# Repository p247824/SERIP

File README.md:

# SERIP — Sistema Embarcado Reativo de Iluminação e Presença

Sistema embarcado desenvolvido na disciplina **EA801 — Laboratório de Projetos de Sistemas Embarcados**, da Faculdade de Engenharia Elétrica e de Computação (FEEC/UNICAMP).

O SERIP combina visualização espectral de áudio em tempo real e controle de iluminação baseado na presença humana, utilizando a plataforma [BitDogLab V7](https://github.com/BitDogLab/BitDogLab), com RP2350. O Projeto 3 consolida a integração do hardware em uma PCB dedicada, mantendo o firmware do Projeto 2.

## Visão geral

### Funcionalidades

- Análise de áudio por FFT de 256 pontos, à frequência de amostragem de 16 kHz.
- Aquisição por ADC e DMA com buffers alternados, processamento em dois núcleos.
- Visualização em matriz de LEDs monocromática 32 × 8, com quatro MAX7219 em cascata.
- Controle automático por sensor radar de presença HLK-LD2410B.
- Modos automático, reativo e desligado, selecionáveis pelo usuário.
- Display OLED com telemetria, gráfico espectral e menu de calibração.
- Placa adaptadora dedicada, eliminando a protoboard utilizada na etapa anterior.

## Evolução do projeto

| Etapa | Desenvolvimento |
| --- | --- |
| Projeto 1 | Protótipo inicial com captação de áudio, matriz de LEDs e interface OLED na BitDogLab. |
| Projeto 2 | Matriz externa MAX7219, radar HLK-LD2410B e expansão da interface e da análise espectral. |
| Projeto 3 | Integração em placa de circuito impresso dedicada, projetada no KiCad para fabricação no SATE/FEEC. |

## Arquitetura

O núcleo 1 do RP2350 é responsável por aquisição do áudio, remoção de offset DC, aplicação da janela Hann e cálculo da FFT. O núcleo 0 gerencia o radar, a comunicação SPI com a matriz, os botões e o OLED. A comunicação entre os núcleos é feita pela FIFO multicore.

| Parâmetro | Valor |
| --- | --- |
| Frequência de amostragem | 16 kHz |
| FFT | 256 pontos |
| Duração de cada bloco | 16 ms |
| Limite de Nyquist | 8 kHz |
| Espaçamento espectral | 62,5 Hz |
| Resolução nominal da matriz | 250 Hz por coluna |
| Comunicação com a matriz | SPI0, 4 MHz |
| Comunicação OLED | I²C1, 400 kHz |

## Hardware

| Componente | Sinal / GPIO |
| --- | --- |
| Microfone MAX4466 (onboard) | GPIO28 — ADC2 |
| Sensor HLK-LD2410B | GPIO4 — OUT |
| Matriz MAX7219 | GPIO17 — CS; GPIO18 — SCK; GPIO19 — DIN |
| OLED SSD1306 | GPIO2 — SDA; GPIO3 — SCL |
| Botão A | GPIO5 |
| Botão B | GPIO6 |
| Botão C | GPIO10 |
| Joystick | GPIO27 — X; GPIO26 — Y |

O sensor e a matriz utilizam alimentação de 5 V e terra comum. A saída digital do radar é de 3,3 V; os pinos UART permanecem sem conexão nesta versão. Confira a correspondência física do IDC de 14 pinos, a polaridade e a orientação dos módulos antes de ligar.

### PCB do Projeto 3

- Dimensões: 52 × 46 mm.
- Face única de cobre (B.Cu), sem vias.
- Largura de trilhas de 0,90 mm, conforme a versão final descrita no relatório.
- J1: interface IDC-14 da BitDogLab.
- J2: conexão da matriz MAX7219.
- J3: conexão do radar HLK-LD2410B (passo de 1,27 mm).
- Plano de terra e contorno de recorte definidos no KiCad.

[Consultar esquemático da PCB](docs/images/esquematico_pcb.png) · [Consultar relatório técnico](docs/Relatorio_Projeto_3.pdf)

O esquemático de montagem do Projeto 2, fornecido com o código, também está disponível em [PDF](docs/esquematico_montagem.pdf) e [SVG](docs/esquematico_montagem.svg). Os arquivos editáveis do KiCad, a biblioteca de footprints e os Gerbers de fabricação do Projeto 3 estão disponíveis em [pcb-prototyping/](pcb-prototyping/). Consulte o [guia do hardware](pcb-prototyping/README.md) para abrir o projeto ou acessar os arquivos de fabricação.

## Implementação física

*Protótipo do Projeto 3 em funcionamento, com os periféricos conectados à BitDogLab V7 por meio da PCB dedicada.*

## Operação

| Comando | Ação |
| --- | --- |
| Botão A | Alterna entre automático (presença → iluminação ambiente, ausência → espera), reativo e desligado. |
| Botão B | Alterna entre painel de estado e gráfico espectral. |
| Botão C | Abre ou fecha o menu de configuração. |
| Joystick Y | Seleciona o parâmetro. |
| Joystick X | Ajusta o valor. |

| Parâmetro | Padrão | Faixa |
| --- | ---: | ---: |
| Limiar de ruído | 20 | 0–500 |
| Teto de energia | 800 | 100–3000 |
| Ganho visual | 1,50 | 0,5–5,0 |
| Velocidade de queda | 1,00 | 0,1–5,0 |

Os ajustes são mantidos em RAM e retornam aos valores padrão após a reinicialização.

## Compilação e gravação

### Pré-requisitos

- BitDogLab V7 com Raspberry Pi Pico 2 W (RP2350).
- Raspberry Pi Pico SDK (o projeto original usa 2.3.1).
- CMake, Ninja e toolchain ARM compatível.
- Opcional: VS Code com a extensão oficial Raspberry Pi Pico.

### Via VS Code

1. Abra a pasta raiz deste repositório.
2. Instale a extensão Raspberry Pi Pico e configure o SDK.
3. Selecione a placa `pico2_w`.
4. Compile o projeto e localize `build/SERIP.uf2`.

### Via terminal

Configure a variável de ambiente `PICO_SDK_PATH` para apontar para uma instalação do [Pico SDK](https://github.com/raspberrypi/pico-sdk) com seus submódulos inicializados e disponibilize a toolchain ARM no PATH.

```bash
cmake -S . -B build -G Ninja -DPICO_BOARD=pico2_w
cmake --build build
```

### Gravação

1. Com a placa desligada, desconecte os periféricos externos, se necessário.
2. Conecte a placa ao USB mantendo pressionado BOOTSEL.
3. Copie `build/SERIP.uf2` para a unidade de armazenamento exibida.
4. Aguarde a reinicialização automática.

Também está disponível o [UF2 original fornecido com o projeto](firmware/SERIP.uf2), preservado sem recompilação.

## Estrutura do repositório

```text
SERIP/
├── README.md
├── CMakeLists.txt
├── pico_sdk_import.cmake
├── main.c
├── ws2812.pio
├── inc/
│   ├── ssd1306.c
│   └── ssd1306.h
├── firmware/
│   └── SERIP.uf2
├── docs/
│   ├── Relatorio_Projeto_3.pdf
│   ├── esquematico_montagem.pdf
│   ├── esquematico_montagem.png
│   ├── esquematico_montagem.svg
│   ├── esquematico_montagem.py
│   └── images/
├── pcb-prototyping/
│   ├── serip2_sate.kicad_pro
│   ├── serip2_sate.kicad_sch
│   ├── serip2_sate.kicad_pcb
│   ├── fp-lib-table
│   ├── serip2_sate.pretty/
│   └── gerbers/
└── .vscode/
```

O código-fonte e os arquivos de configuração do pacote original foram preservados; arquivos temporários de compilação foram omitidos. A presença do arquivo UF2 original não representa uma nova validação de compilação.

## Documentação e validação

- [Relatório completo do Projeto 3 (PDF)](docs/Relatorio_Projeto_3.pdf)
- [Esquemático de montagem anterior (Projeto 2)](docs/esquematico_montagem.pdf)
- [Guia de validação da PCB](docs/VALIDACAO.md)
- [Projeto KiCad e arquivos de fabricação](pcb-prototyping/README.md)

**Estado atual:** sistema integrado à PCB dedicada e operando conforme as funcionalidades previstas do Projeto 3. O firmware disponibilizado é o SERIP 2, reaproveitado nesta etapa.

## Referências

- [BitDogLab — repositório oficial](https://github.com/BitDogLab/BitDogLab)
- [RP2350 — datasheet](https://datasheets.raspberrypi.com/rp2350/rp2350-datasheet.pdf)
- [Raspberry Pi Pico SDK](https://github.com/raspberrypi/pico-sdk)
- [MAX7219/MAX7221 — datasheet](https://www.analog.com/media/en/technical-documentation/data-sheets/MAX7219-MAX7221.pdf)
- [Hi-Link — HLK-LD2410B, protocolo e pinagem](https://r0.hlktech.com/download/HLK-LD2410B-24G/1/LD2410B%20%E4%B8%B2%E5%8F%A3%E9%80%9A%E4%BF%A1%E5%8D%8F%E8%AE%AE%20V1.08.pdf)
- [KiCad](https://www.kicad.org/)

## Autores

- **Fernando Cesar Rodrigues da Silva**
- **Pedro da Costa Viana**

FEEC — Universidade Estadual de Campinas (UNICAMP), 2026.

Projeto acadêmico. Nenhuma licença própria foi declarada pelos autores no pacote original; os componentes de terceiros mantêm suas respectivas condições de uso.

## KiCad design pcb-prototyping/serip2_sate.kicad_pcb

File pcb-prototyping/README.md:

# PCB dedicada — SERIP / Projeto 3

Placa adaptadora desenvolvida para integrar a BitDogLab V7, a matriz MAX7219 de 32 × 8 LEDs e o sensor de presença HLK-LD2410B, substituindo a protoboard do Projeto 2.

## Arquivos de projeto

| Arquivo | Descrição |
| --- | --- |
| [serip2_sate.kicad_pro](serip2_sate.kicad_pro) | Projeto KiCad e regras de projeto |
| [serip2_sate.kicad_sch](serip2_sate.kicad_sch) | Esquemático elétrico |
| [serip2_sate.kicad_pcb](serip2_sate.kicad_pcb) | Layout da placa |
| [fp-lib-table](fp-lib-table) | Tabela da biblioteca local |
| [serip2_sate.pretty/](serip2_sate.pretty/) | Footprints personalizados dos conectores J1, J2 e J3 |
| [gerbers/](gerbers/) | Arquivos de fabricação Gerber e Excellon |

## Abrindo no KiCad

1. Baixe o repositório completo (Code → Download ZIP) ou clone-o.
2. Utilize o KiCad **10.0** ou uma versão compatível com os arquivos de origem.
3. Abra `serip2_sate.kicad_pro` nesta pasta.
4. Mantenha `fp-lib-table` e `serip2_sate.pretty/` junto ao projeto para carregar os footprints locais.

Os arquivos originais de projeto foram preservados. Arquivos temporários, bloqueios de edição e histórico interno não fazem parte do pacote.

## Fabricação

O layout foi desenvolvido para fresagem em face única no SATE/FEEC-UNICAMP: cobre ativo em B.Cu, 25 segmentos de trilha de 0,90 mm e nenhuma via, conforme o projeto original.

| Arquivo | Finalidade |
| --- | --- |
| [B_Cu](gerbers/serip2_sate-B_Cu.gbr) | Cobre inferior |
| [B_Mask](gerbers/serip2_sate-B_Mask.gbr) | Máscara inferior |
| [Edge_Cuts](gerbers/serip2_sate-Edge_Cuts.gbr) | Contorno da placa |
| [PTH.drl](gerbers/serip2_sate-PTH.drl) | Furação de componentes |
| [NPTH.drl](gerbers/serip2_sate-NPTH.drl) | Arquivo complementar de furação não metalizada |
| [gbrjob](gerbers/serip2_sate-job.gbrjob) | Metadados do conjunto Gerber |

A fabricação no SATE deve seguir as especificações do relatório (face única, sem metalização de furos), independentemente da classificação exportada pelo KiCad. Antes de fabricar uma nova unidade, confira o conjunto de Gerbers no visualizador e confirme a pinagem e polaridade da montagem.

[Relatório técnico completo](../docs/Relatorio_Projeto_3.pdf) · [Guia de validação](../docs/VALIDACAO.md)

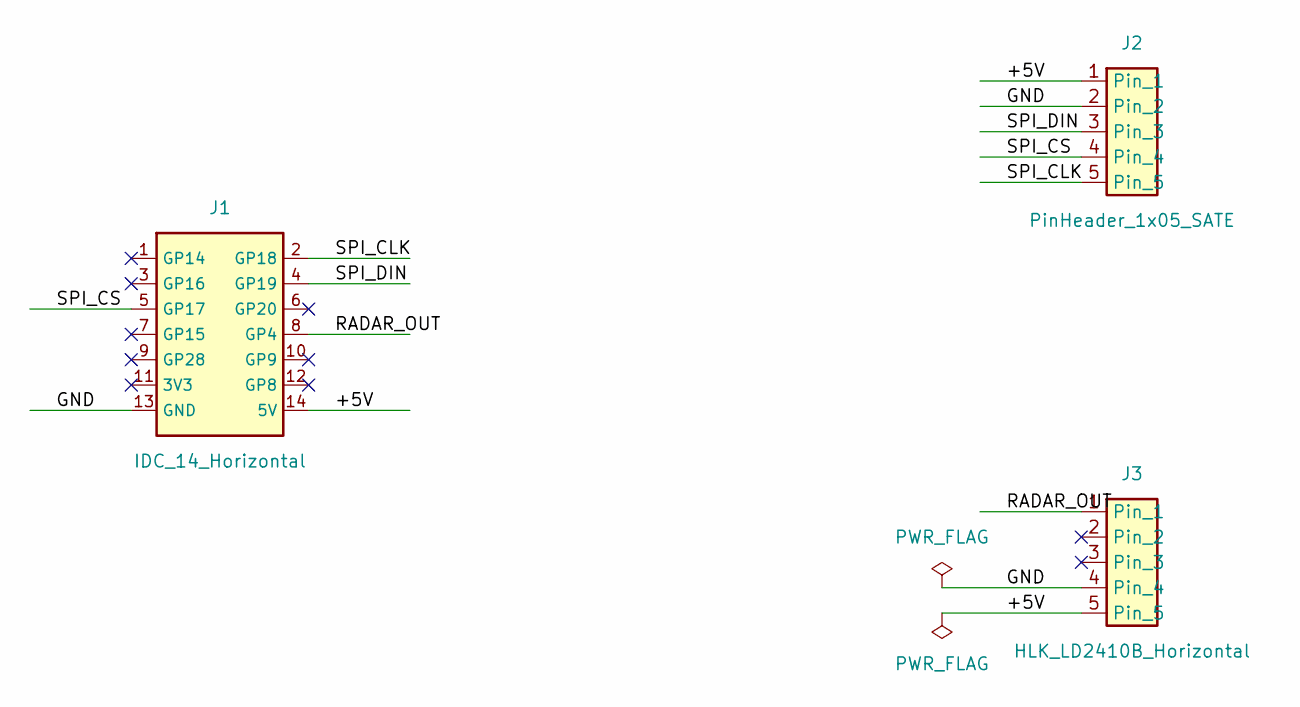
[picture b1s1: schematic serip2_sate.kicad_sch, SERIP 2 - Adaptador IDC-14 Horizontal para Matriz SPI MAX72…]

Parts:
J1: IDC_14_Horizontal
J2: PinHeader_1x05_SATE
J3: HLK_LD2410B_Horizontal

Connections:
/+5V: J1.14 (5V), J2.1, J3.5
/GND: J1.13 (GND), J2.2, J3.4
/RADAR_OUT: J1.8 (GP4), J3.1
/SPI_CLK: J1.2 (GP18), J2.5
/SPI_CS: J1.5 (GP17), J2.4
/SPI_DIN: J1.4 (GP19), J2.3

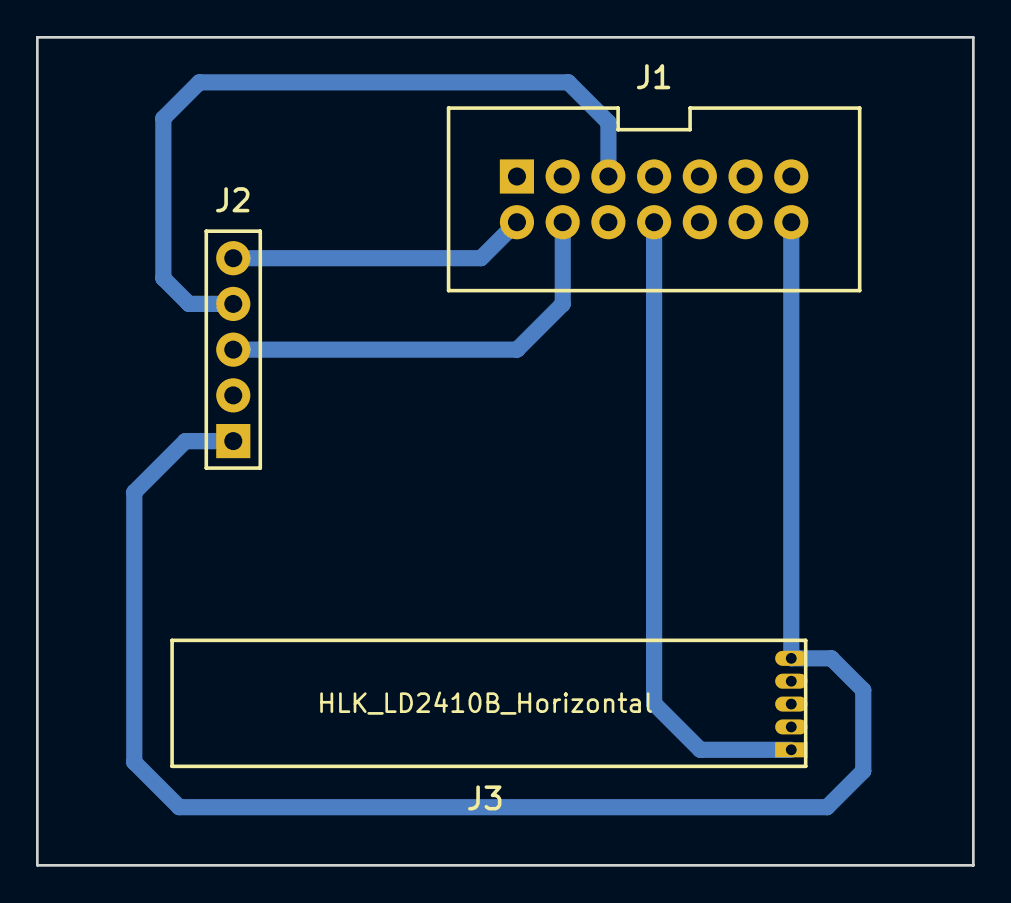
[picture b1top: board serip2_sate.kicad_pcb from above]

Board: 2 copper layers, 52.0 x 46.0 mm, 3 parts (0 on the bottom side), 6 nets.
